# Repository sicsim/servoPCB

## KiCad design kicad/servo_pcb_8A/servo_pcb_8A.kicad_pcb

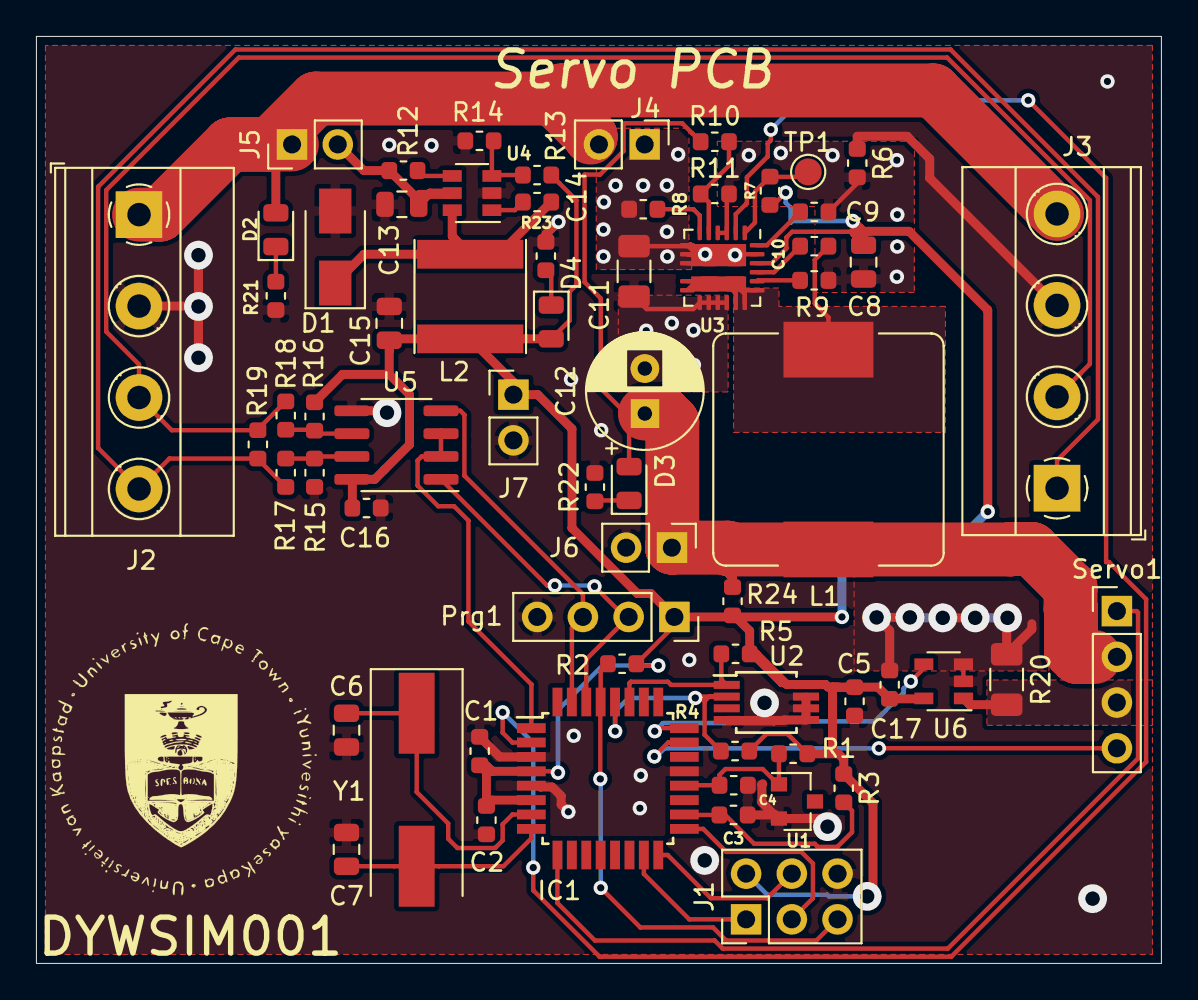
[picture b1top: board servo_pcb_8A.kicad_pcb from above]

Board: 2 copper layers, 62.5 x 51.5 mm, 65 parts (0 on the bottom side), 43 nets.

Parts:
C1, C2, C3, C5, C10, C14, C16, C17: 0.1uF; C_0603_1608Metric
C4: 1uF; C_0603_1608Metric
C6, C7: 22pF; C_0805_2012Metric
C8, C13: 4.7uF; C_0805_2012Metric
C9: 0.01uF; C_0603_1608Metric
C11: 22uF; C_1206_3216Metric
C12: 88uF; CP_Radial_D6.3mm_P2.50mm
C15: 10uF; C_0805_2012Metric
D1: D_Schottky; D_SMA
D2, D3, D4: LED; LED_0805_2012Metric
IC1: ATMEGA328P-A; TQFP-32_7x7mm_P0.8mm
J1: Conn_02x03_Odd_Even; PinHeader_2x03_P2.54mm_Vertical
J2, J3: Term_Block; TerminalBlock_Phoenix_MKDS-1,5-4-5.08_1x04_P5.08mm_Horizont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
J4, J5, J6, J7: Conn_01x02; PinHeader_1x02_P2.54mm_Vertical
L1: 1uH; L_Bourns_SRP1245A
L2: 22uH; L_Taiyo-Yuden_NR-60xx
Prg1: Conn_01x04; PinSocket_1x04_P2.54mm_Vertical
R1, R2: 1K; R_0603_1608Metric
R3, R6, R24: 0R; R_0603_1608Metric
R4, R5, R11, R12, R14: 10K; R_0603_1608Metric
R7, R8: 100K; R_0603_1608Metric
R9: 9K1; R_0603_1608Metric
R10: 210K_220K_270K_340K; R_0603_1608Metric
R13: 52K3; R_0603_1608Metric
R15, R16, R22, R23: 560R; R_0603_1608Metric
R17, R18: 10R; R_0603_1608Metric
R19: 120R; R_0603_1608Metric
R20: 0.002R; R_1206_3216Metric
R21: 2K2; R_0603_1608Metric
Servo1: Conn_01x04; PinHeader_1x04_P2.54mm_Vertical
TP1: testpoint; TestPoint_Pad_D1.5mm
U1: LM4040D20IDBZR; SOT-23
U2: LM75C; MSOP-8_3x3mm_P0.65mm
U3: AOZ2261NQI-11
U4: AOZ1282CI; SOT-23-6
U5: MAX485E; SOIC-8_3.9x4.9mm_P1.27mm
U6: INA180B2IBVR; SOT-23-5
Y1: 16MHz; Crystal_SMD_HC49-SD

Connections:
5V: C1.1, C2.1, C5.1, C8.1, C15.1, C16.1, C17.1, D4.2, IC1.4, IC1.6, J1.2, J7.1, L2.2, Prg1.1, R1.1, R2.1, R3.1, R4.1, R5.1, R7.1, R13.1, R16.2, R24.2, U2.8, U3.21, U5.8, U6.5
A: J2.3, J3.2, R18.1, R19.2
AGND_8A: C8.2, C9.2, R6.2, R9.2, R11.2, U3.3, U3.4
B: J2.4, J3.1, R17.1, R19.1
EN_8A: IC1.2, U3.2
EN_RS485: IC1.1, U5.2, U5.3
GND: C1.2, C2.2, C3.2, C4.2, C5.2, C6.1, C7.2, C11.2, C12.2, C13.2, C15.2, C16.2, C17.2, D1.2, IC1.3, IC1.5, IC1.21, J1.6, J2.2, J3.3, J6.2, J7.2, Prg1.4, R6.1, R14.2, R15.2, R20.2, R21.2, R22.2, R23.2, U1.2, U2.4, U2.5, U2.6, U2.7, U3.12, U3.13, U3.14, U3.15, U4.2, U5.5, U6.2, U6.3
GND_S: R20.1, Servo1.3, U6.1
I_Sense: IC1.24, U6.4
MISO: IC1.15, J1.1
MOSI: IC1.16, J1.4
unnamed: C3.1, IC1.18, R3.2
unnamed: C4.1, IC1.20, R1.2, U1.1
unnamed: C6.2, IC1.7, Y1.1
unnamed: C7.1, IC1.8, Y1.2
unnamed: C9.1, U3.23
unnamed: C10.1, L1.1, U3.10, U3.11, U3.16, U3.17, U3.18, U3.P2
unnamed: C10.2, U3.20
unnamed: C11.1, J4.1, R8.1, U3.7, U3.8, U3.9, U3.22, U3.P1
unnamed: C13.1, J5.2, R12.1, U4.5
unnamed: C14.1, D1.1, L2.1, U4.6
unnamed: C14.2, U4.1
unnamed: D2.1, R21.1
unnamed: D3.1, R22.1
unnamed: D4.1, R23.1
unnamed: R7.2, TP1.1, U3.1
unnamed: R8.2, U3.6
unnamed: R9.1, U3.19
unnamed: R10.2, R11.1, U3.5
unnamed: R12.2, U4.4
unnamed: R13.2, R14.1, U4.3
unnamed: R15.1, R17.2, U5.7
unnamed: R16.1, R18.2, U5.6
P_Sense: IC1.23, Servo1.4
RESET: IC1.29, J1.5, R2.2
RX: IC1.30, Prg1.2, U5.1
SCK: IC1.17, J1.3
SCL: IC1.28, R4.2, U2.2
SDA: IC1.27, R5.2, U2.1
TX: IC1.31, Prg1.3, U5.4
V_Servo: C12.1, D3.2, J6.1, L1.2, R10.1, R24.1, Servo1.2
V_in: D2.2, J2.1, J3.4, J4.2, J5.1
servo_com: IC1.9, Servo1.1

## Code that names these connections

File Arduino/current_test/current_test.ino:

/* Institution:   University of Cape Town
   Author:        Simplicity S Dywili
   Date:          26 September 2019
   Project:       Servo PCB
*/

#include <Arduino.h>
#include <Wire.h>
#include <TimerOne.h>
#include <Temperature_LM75_Derived.h>
#include <Servo.h>

#define P_sense A0
#define I_sense A1
#define EN_RS485 3
#define EN_8A 4
#define Servo_com 5

//Initialising objects/classes
Generic_LM75 temperature;
Servo myservo;  

//Initialise variables
float Sensing_Resistor=0.002;  //Ohms
int Amplifier_Gain=50;        //

int Current_ADC_value=0;
float Current_Amperes=0;
int Position_ADC_value=0;
int Position_Degrees=0;
float PCB_Temperature=25.55;

int pos=0; //Used by the servo

//***********************************Setting up*****************************************
void setup() {
  pinMode(EN_RS485, OUTPUT);
  pinMode(EN_8A, OUTPUT);
  pinMode(Servo_com, OUTPUT);
  digitalWrite(EN_8A,HIGH);
  digitalWrite(EN_RS485,LOW);
  
  Serial.begin(115200);   //Serial Monitor

  //Change the ADC reference voltage to external;
  analogReference(EXTERNAL);
  
  Serial.println("Setup Complete");
  delay(100);
}


//***********************************MAIN LOOP*****************************************
void loop() {
  Serial.print( "Current Amps : \t");
  Serial.println(ADC_to_Amperes());
  delay(250); //delay 250 milliseconds
}

//Function to convert the ADC value to current in Amperes
float ADC_to_Amperes(){
  Current_ADC_value = analogRead(I_sense);
  float ADC_voltage = (((Current_ADC_value*1.0F)/1024)*2.048);  //Voltage to to the ADC input
  float Sensing_resistor_voltage =  ADC_voltage/Amplifier_Gain; //Voltage drop across the sensing resistor
  Current_Amperes =  Sensing_resistor_voltage/Sensing_Resistor; //Actual current through the sensing resistor
  return Current_Amperes;
}
